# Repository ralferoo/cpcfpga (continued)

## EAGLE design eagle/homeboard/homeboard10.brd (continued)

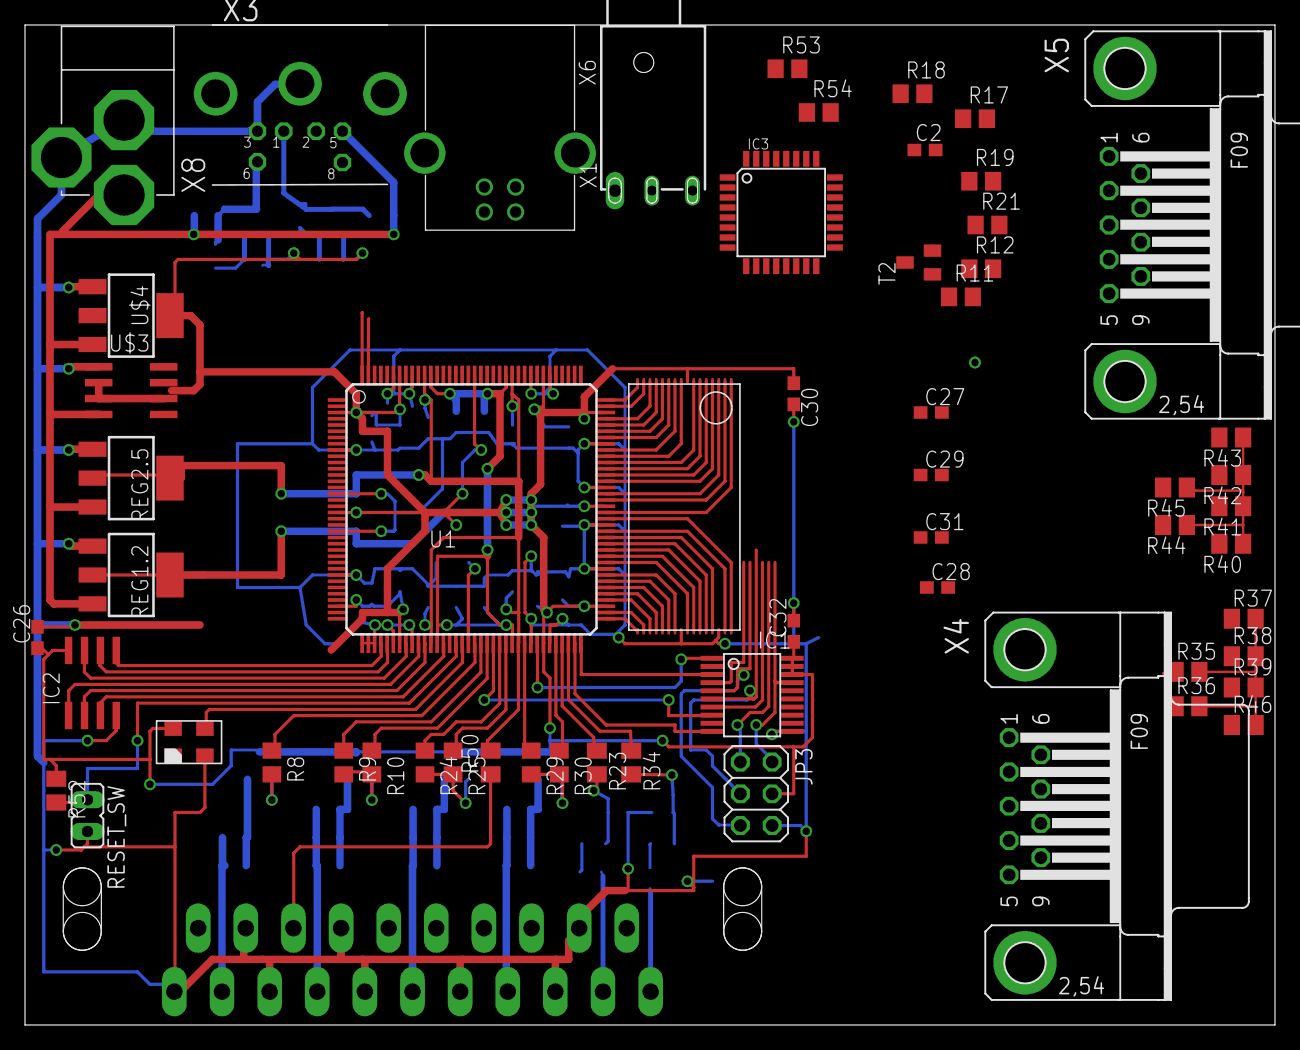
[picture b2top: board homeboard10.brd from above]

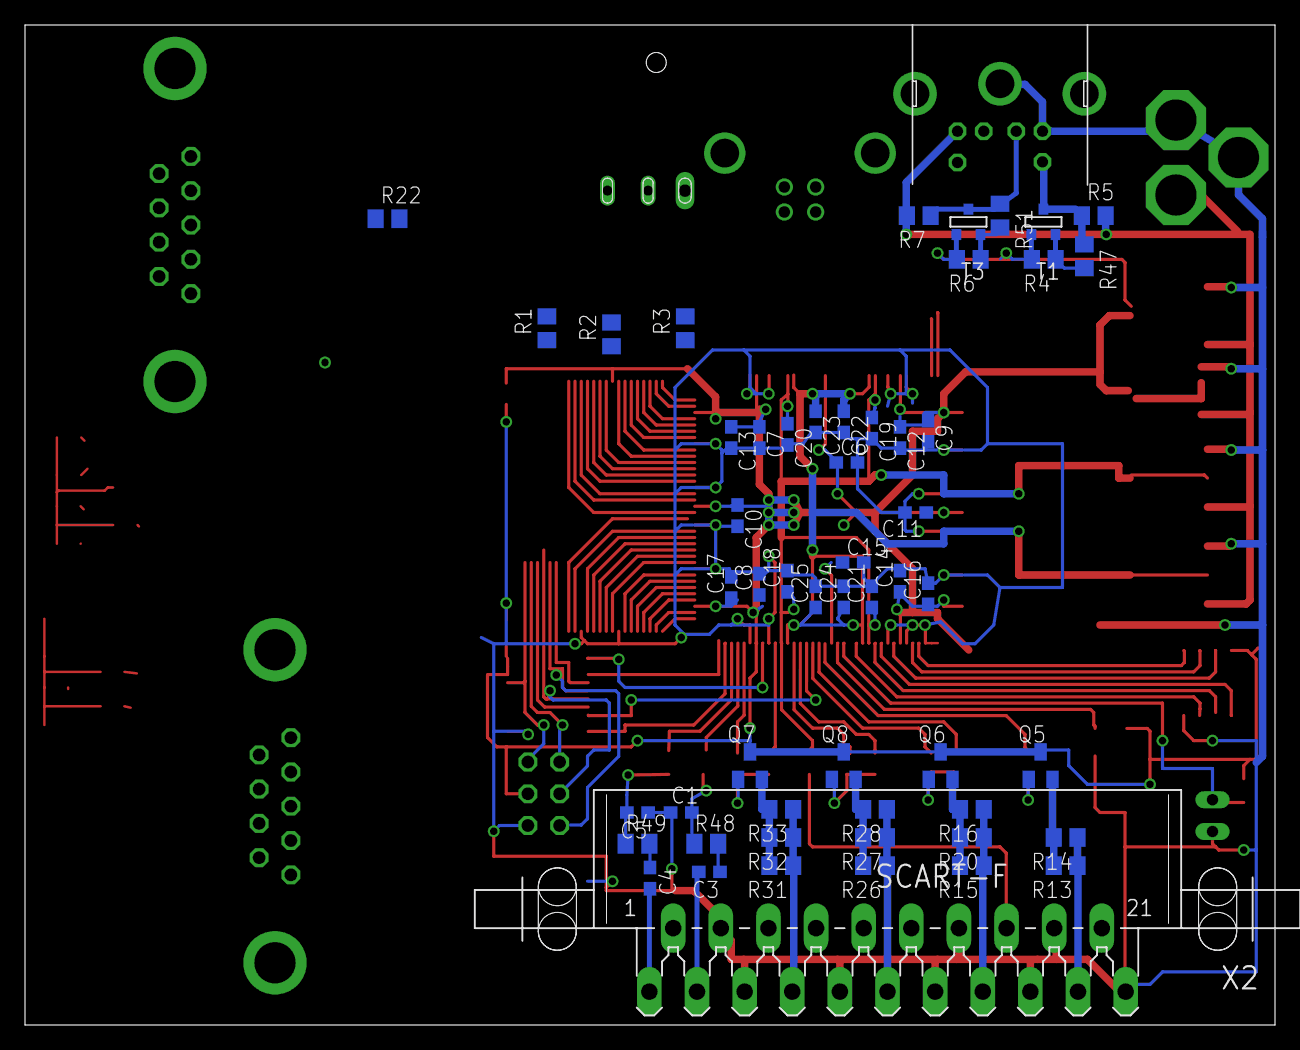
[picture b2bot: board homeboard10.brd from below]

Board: 2 copper layers, 100.0 x 80.0 mm, 112 parts (54 on the bottom side), 110 nets.
